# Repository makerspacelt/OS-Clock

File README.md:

# OS-Clock
Repository has information off how to build big portable LED clock.

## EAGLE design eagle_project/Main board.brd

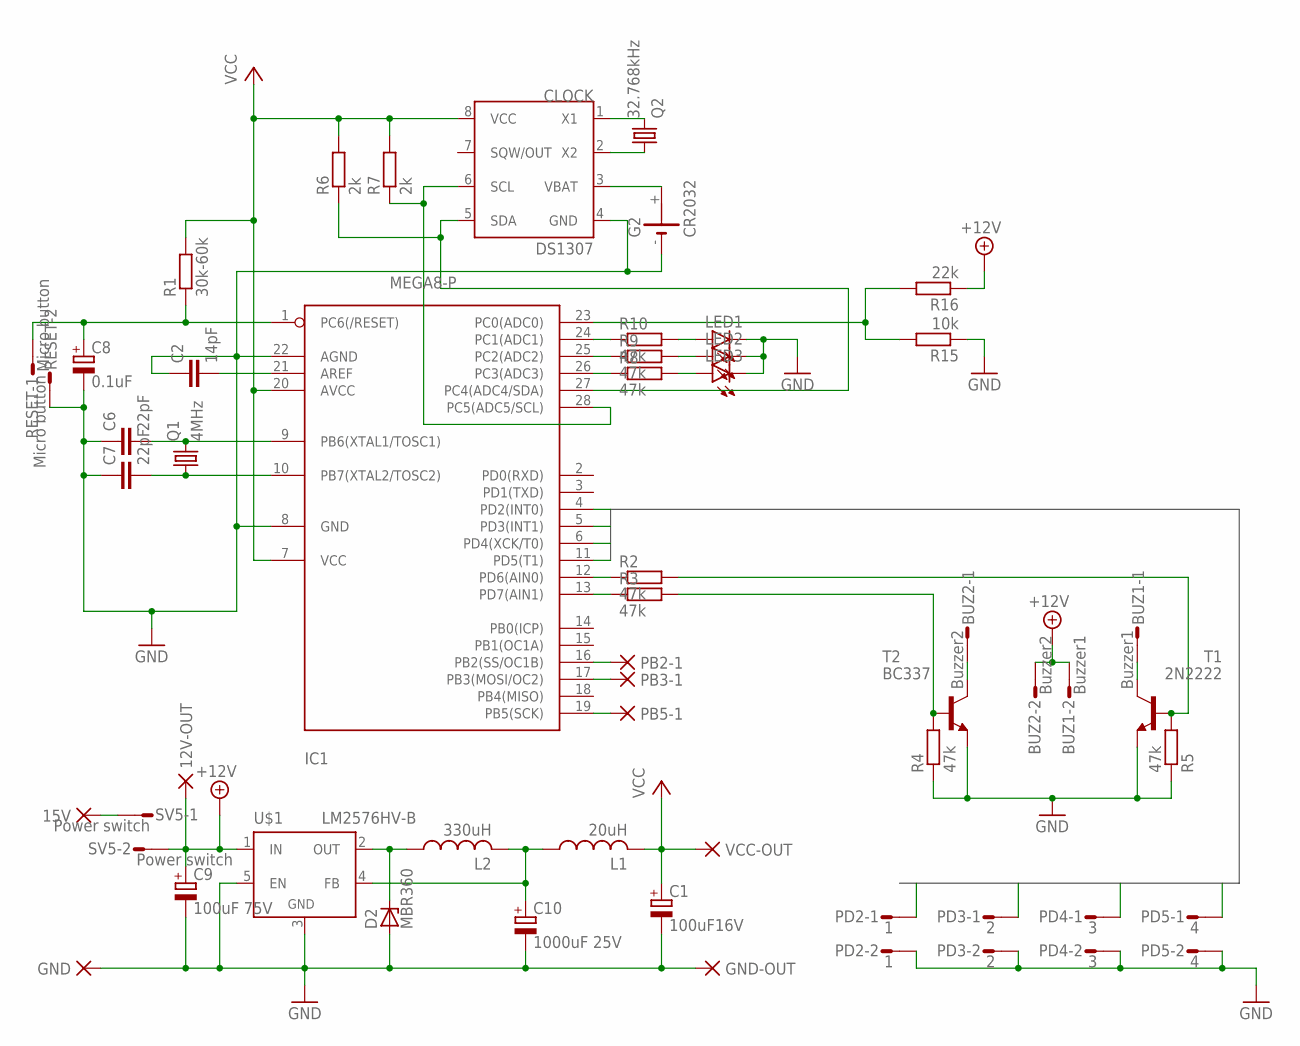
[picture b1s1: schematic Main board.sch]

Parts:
12V-OUT, 15V: PAD-0500; 0500
BUZ1: Buzzer1; S02P
BUZ2: Buzzer2; S02P
C1: 100uF16V; E2,5-6
C2: 14pF; C102-054X133
C6, C7: 22pF; C025-030X050
C8: 0.1uF; E2,5-6
C9: 100uF 75V; E5-10,5
C10: 1000uF 25V; E5-10,5
CLOCK: DS1307; SOIC-8
D2: MBR360; C1702-15
G2: CR2032; CR2032-20MM
GND: PAD-0500; 0500
GND-OUT: PAD-0500; 0500
IC1: MEGA8-P; DIL28-3
L1: 20uH; TJ3-U1
L2: 330uH; TJ3-U1
LED1, LED2, LED3: LED5MM
PB2-1, PB3-1, PB5-1: PAD-0400; 0400
PD2: 1; S02P
PD3: 2; S02P
PD4: 3; S02P
PD5: 4; S02P
Q1: 4MHz; HC49U-V
Q2: 32.768kHz; CRYSTAL
R1: 30k-60k; 0309/15
R2, R3, R4, R5, R8, R9, R10: 47k; 0309/15
R6, R7: 2k; 0309/15
R15: 10k; 0309/15
R16: 22k; 0309/15
RESET: Micro button; S02P
SV5: Power switch; S02P
T1: 2N2222; TO18
T2: BC337; TO92
U$1: LM2576HV-B; TO220-53
VCC-OUT: PAD-0500; 0500

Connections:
+12V: 12V-OUT.P$1, BUZ1.2, BUZ2.2, C9.+, R16.1, SV5.2, U$1.1 (IN)
GND: C1.-, C2.1, C6.1, C7.1, C8.-, C9.-, C10.-, CLOCK.4 (GND), D2.A, G2.-, GND.P$1, GND-OUT.P$1, IC1.8 (GND), IC1.22 (AGND), LED1.K (C), LED2.K (C), LED3.K (C), PD2.2, PD3.2, PD4.2, PD5.2, R4.1, R5.1, R15.1, RESET.2, T1.1 (E), T2.1 (E), U$1.3 (GND), U$1.5 (EN)
unnamed: CLOCK.1 (X1), Q2.2
unnamed: 15V.P$1, SV5.1
unnamed: CLOCK.2 (X2), Q2.1
unnamed: IC1.24 (PC1(ADC1)), R10.1
unnamed: IC1.25 (PC2(ADC2)), R9.1
unnamed: IC1.26 (PC3(ADC3)), R8.1
unnamed: LED1.A, R10.2
unnamed: LED2.A, R9.2
unnamed: LED3.A, R8.2
unnamed: C2.2, IC1.21 (AREF)
unnamed: C6.2, IC1.9 (PB6(XTAL1/TOSC1)), Q1.2
unnamed: C7.2, IC1.10 (PB7(XTAL2/TOSC2)), Q1.1
unnamed: C8.+, IC1.1 (PC6(/RESET)), R1.1, RESET.1
unnamed: CLOCK.6 (SCL), IC1.28 (PC5(ADC5/SCL)), R7.1
unnamed: IC1.23 (PC0(ADC0)), R15.2, R16.2
unnamed: CLOCK.5 (SDA), IC1.27 (PC4(ADC4/SDA)), R6.1
unnamed: IC1.12 (PD6(AIN0)), R2.1
unnamed: IC1.13 (PD7(AIN1)), R3.1
unnamed: BUZ2.1, T2.3 (C)
unnamed: R3.2, R4.2, T2.2 (B)
unnamed: R2.2, R5.2, T1.2 (B)
unnamed: BUZ1.1, T1.3 (C)
unnamed: IC1.16 (PB2(SS/OC1B)), PB2-1.P$1
unnamed: C10.+, L1.1, L2.2, U$1.4 (FB)
unnamed: D2.C, L2.1, U$1.2 (OUT)
unnamed: IC1.17 (PB3(MOSI/OC2)), PB3-1.P$1
unnamed: IC1.19 (PB5(SCK)), PB5-1.P$1
PD2: IC1.4 (PD2(INT0)), PD2.1
PD3: IC1.5 (PD3(INT1)), PD3.1
PD4: IC1.6 (PD4(XCK/T0)), PD4.1
PD5: IC1.11 (PD5(T1)), PD5.1
VBAT: CLOCK.3 (VBAT), G2.+
VCC: C1.+, CLOCK.8 (VCC), IC1.7 (VCC), IC1.20 (AVCC), L1.2, R1.2, R6.2, R7.2, VCC-OUT.P$1

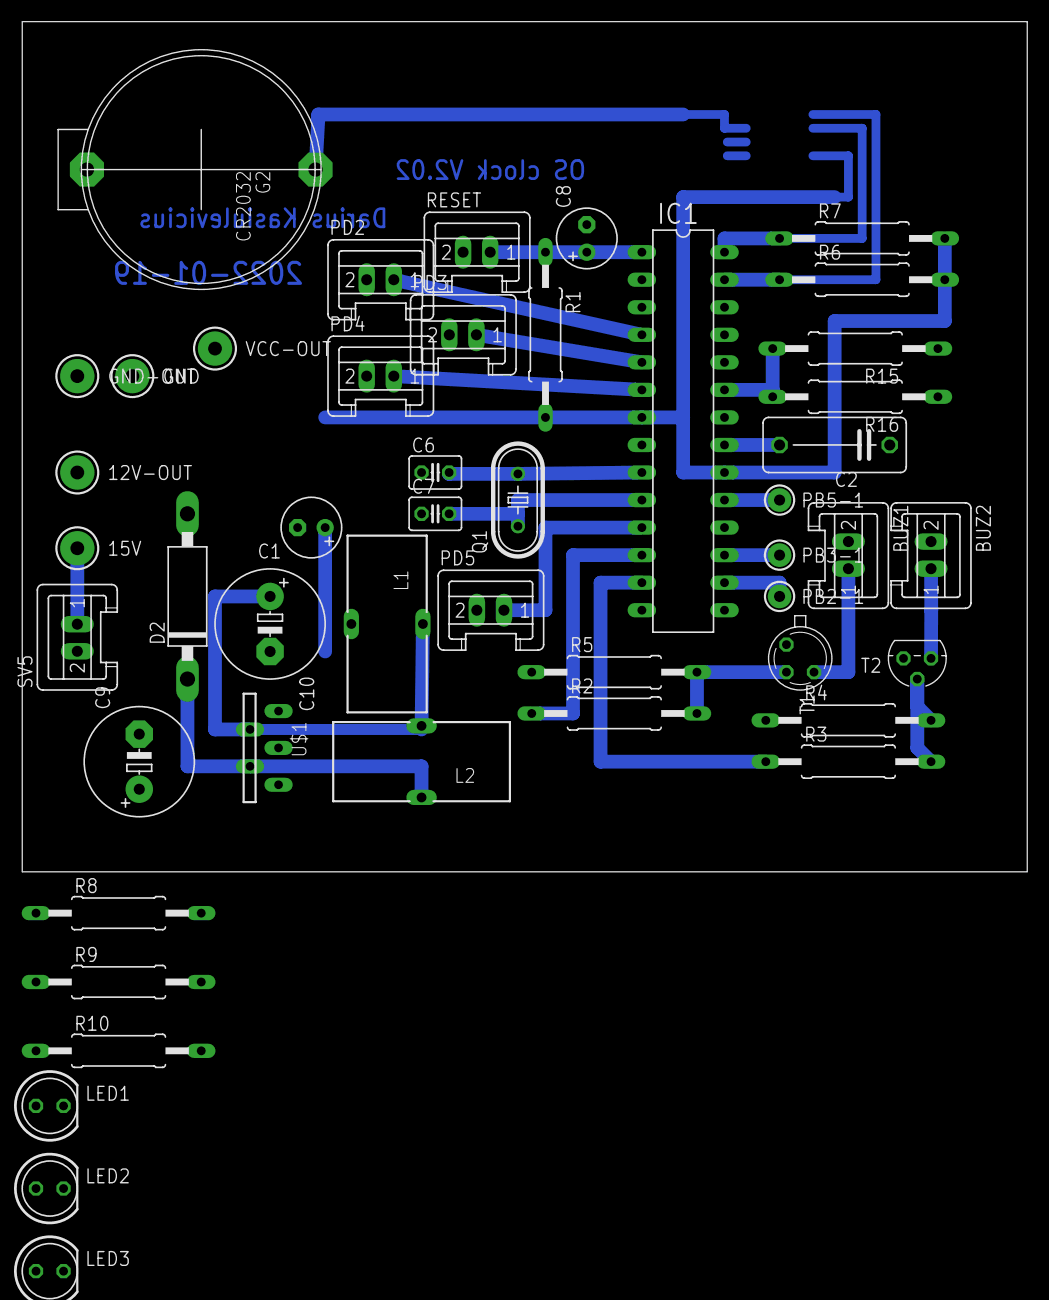
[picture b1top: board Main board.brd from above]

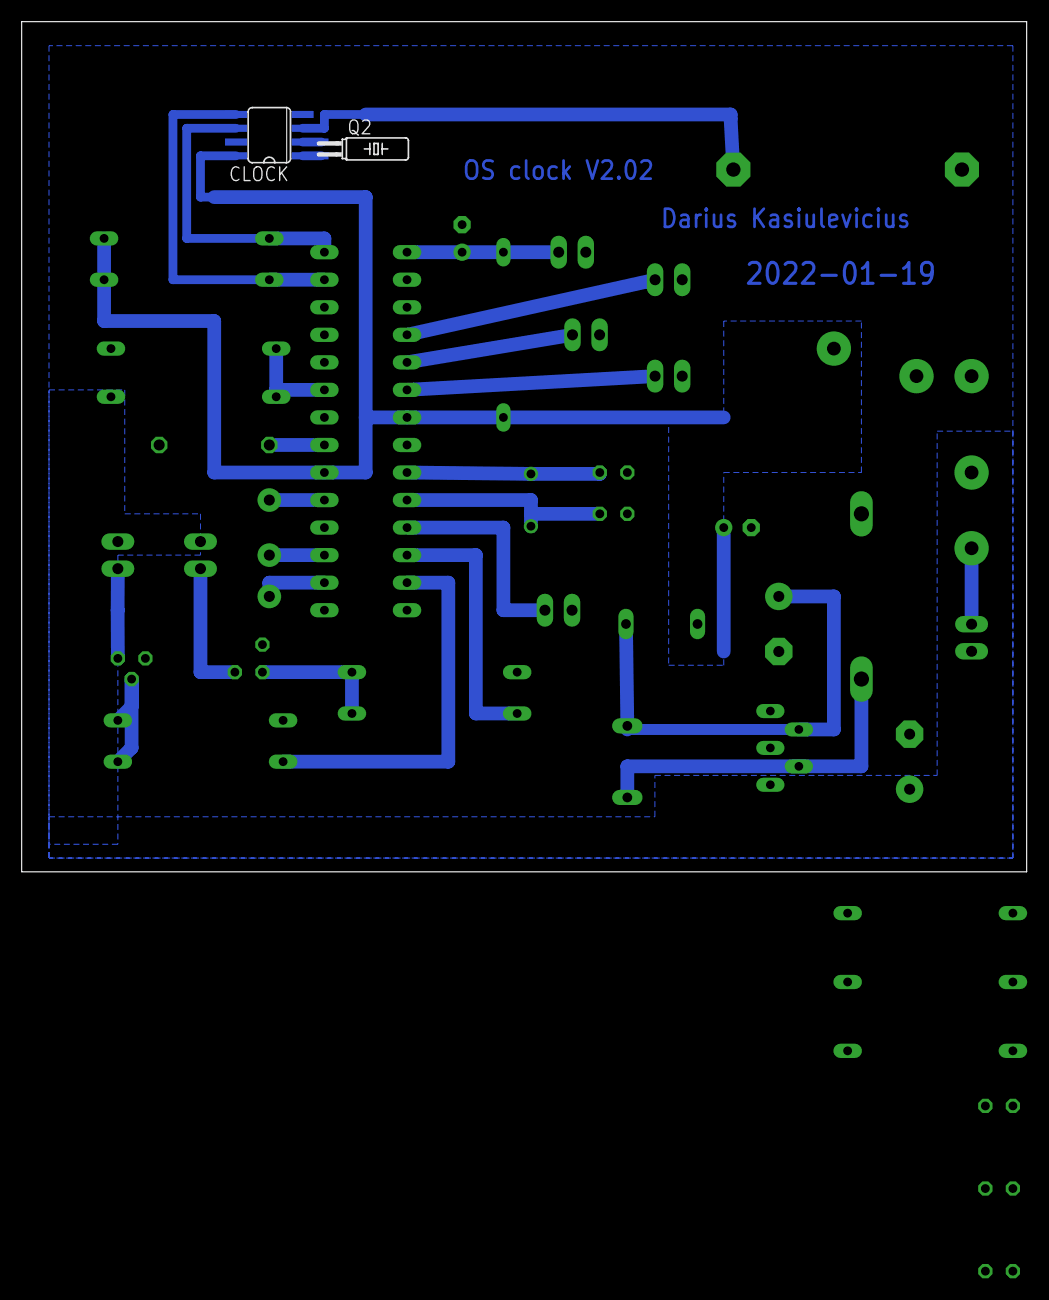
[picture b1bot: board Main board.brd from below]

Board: 2 copper layers, 92.7 x 78.4 mm, 49 parts (2 on the bottom side), 35 nets.

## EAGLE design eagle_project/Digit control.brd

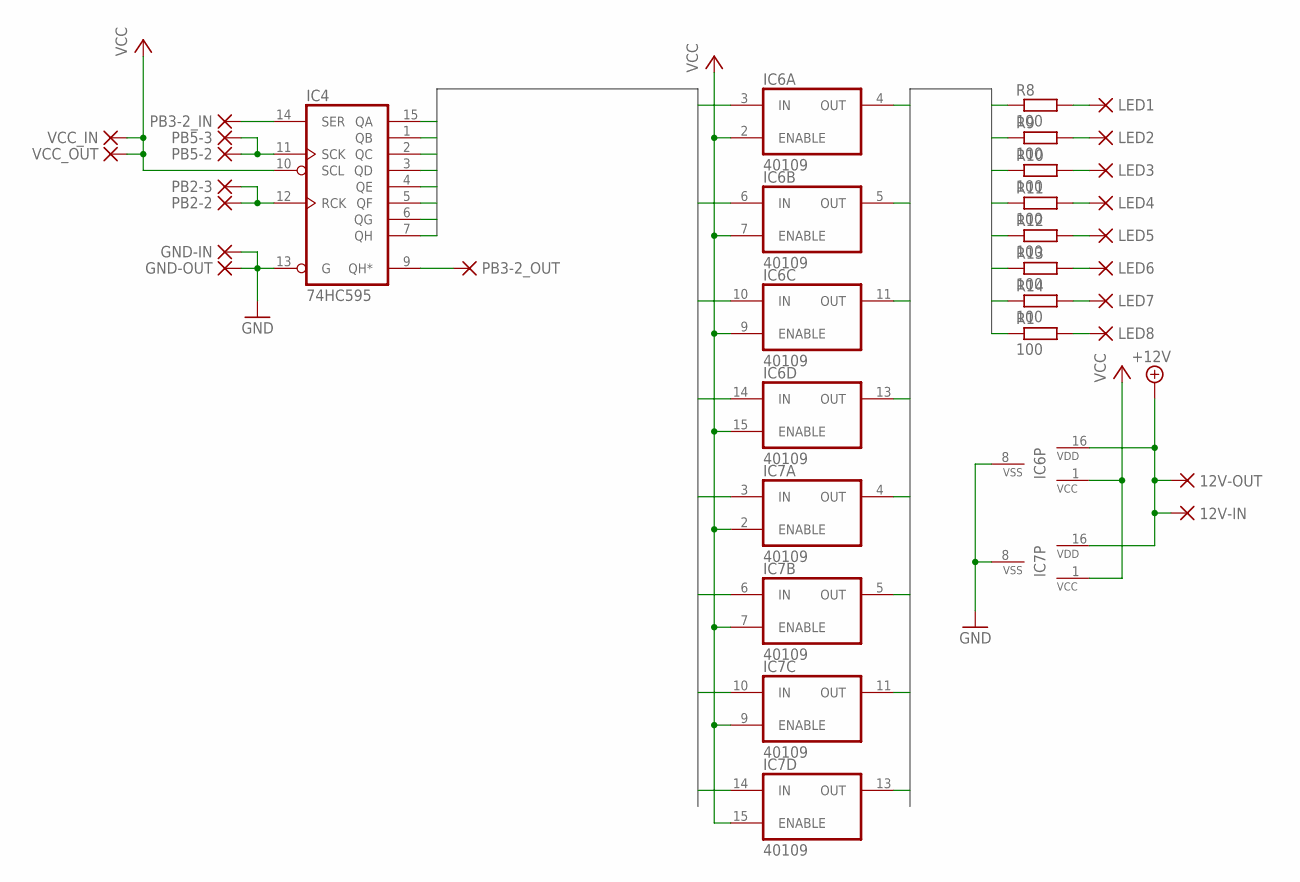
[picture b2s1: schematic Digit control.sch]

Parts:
12V-IN, 12V-OUT: PAD-0500; 0500
GND-IN: PAD-0500; 0500
GND-OUT: PAD-0820; 0820
IC4: 74HC595; DIL16
IC6, IC7: 40109; DIL16
LED1, LED2, LED3, LED4, LED5, LED6, LED7, LED8: PAD-0400; 0400
PB2-2, PB2-3, PB3-2_IN, PB3-2_OUT, PB5-2, PB5-3: PAD-0400; 0400
R1, R8, R9, R10, R11, R12, R13, R14: 100; 0309/15
VCC_IN: PAD-0500; 0500
VCC_OUT: PAD-0500; 0500

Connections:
+12V: 12V-IN.P$1, 12V-OUT.P$1, IC6.16 (VDD), IC7.16 (VDD)
GND: GND-IN.P$1, GND-OUT.P$1, IC4.8 (GND), IC4.13 (G), IC6.8 (VSS), IC7.8 (VSS)
LED1: IC6.4 (OUT), R8.1
LED2: IC6.5 (OUT), R9.1
LED3: IC6.11 (OUT), R10.1
LED4: IC6.13 (OUT), R11.1
LED5: IC7.4 (OUT), R12.1
LED6: IC7.5 (OUT), R13.1
LED7: IC7.11 (OUT), R14.1
LED8: IC7.13 (OUT), R1.1
LED_INPUT1: IC4.15 (QA), IC6.3 (IN)
LED_INPUT2: IC4.1 (QB), IC6.6 (IN)
LED_INPUT3: IC4.2 (QC), IC6.10 (IN)
LED_INPUT4: IC4.3 (QD), IC6.14 (IN)
LED_INPUT5: IC4.4 (QE), IC7.3 (IN)
LED_INPUT6: IC4.5 (QF), IC7.6 (IN)
LED_INPUT7: IC4.6 (QG), IC7.10 (IN)
LED_INPUT8: IC4.7 (QH), IC7.14 (IN)
unnamed: IC4.14 (SER), PB3-2_IN.P$1
unnamed: LED1.P$1, R8.2
unnamed: IC4.11 (SCK), PB5-2.P$1, PB5-3.P$1
unnamed: IC4.12 (RCK), PB2-2.P$1, PB2-3.P$1
unnamed: IC4.9 (QH*), PB3-2_OUT.P$1
unnamed: LED7.P$1, R14.2
unnamed: LED6.P$1, R13.2
unnamed: LED5.P$1, R12.2
unnamed: LED4.P$1, R11.2
unnamed: LED3.P$1, R10.2
unnamed: LED2.P$1, R9.2
unnamed: LED8.P$1, R1.2
VCC: IC4.10 (SCL), IC4.16 (VCC), IC6.1 (VCC), IC6.2 (ENABLE), IC6.7 (ENABLE), IC6.9 (ENABLE), IC6.15 (ENABLE), IC7.1 (VCC), IC7.2 (ENABLE), IC7.7 (ENABLE), IC7.9 (ENABLE), IC7.15 (ENABLE), VCC_IN.P$1, VCC_OUT.P$1

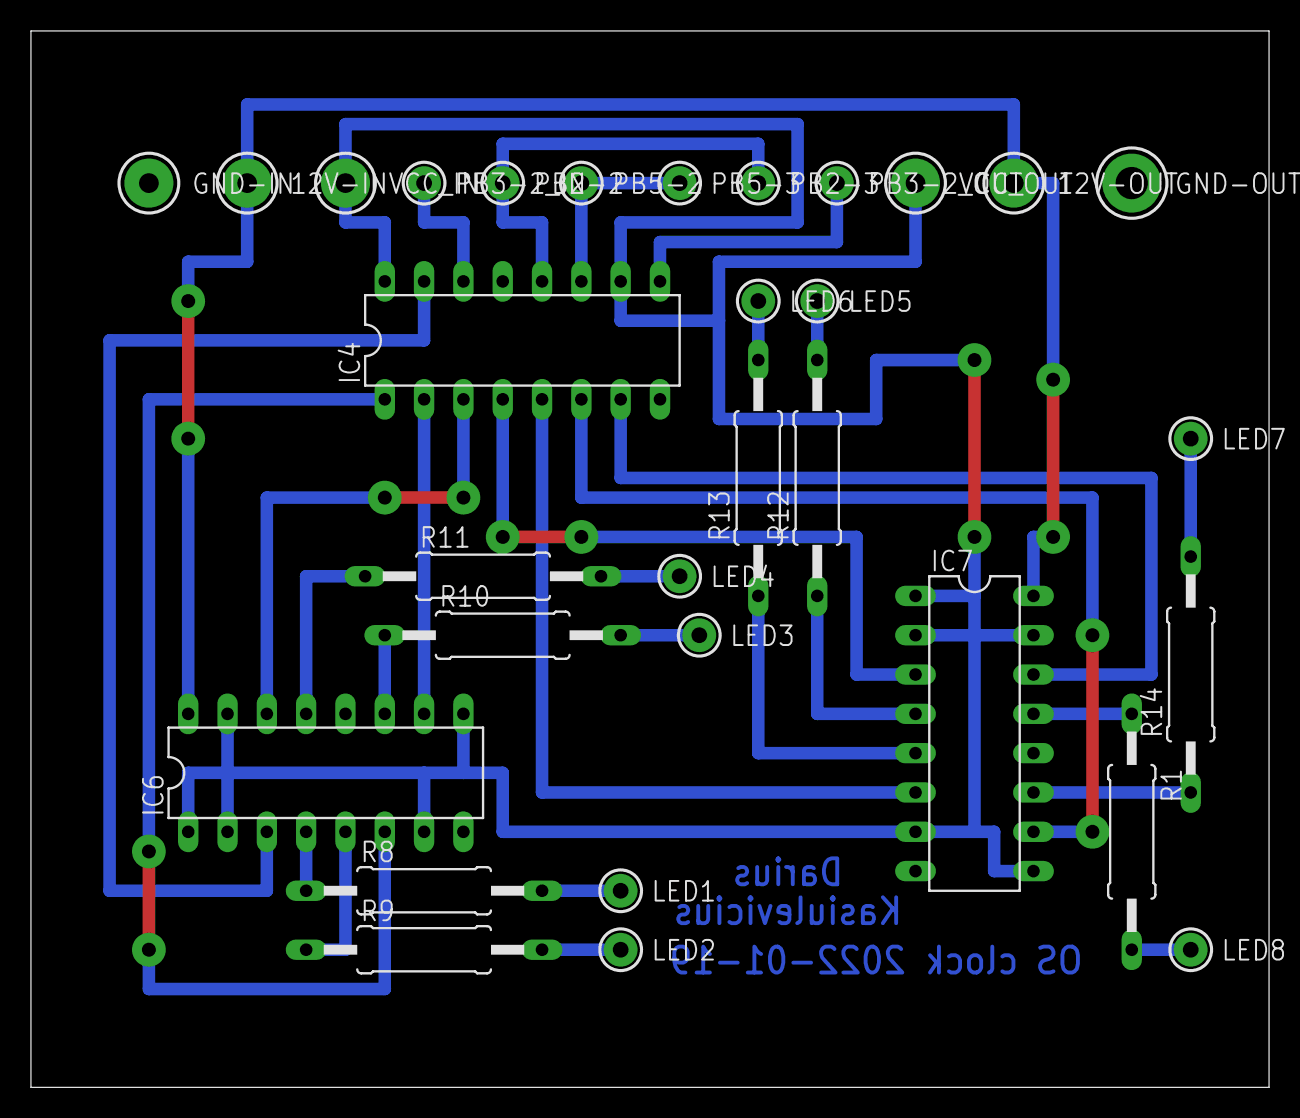
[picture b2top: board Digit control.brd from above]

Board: 2 copper layers, 80.0 x 68.2 mm, 31 parts (0 on the bottom side), 31 nets.

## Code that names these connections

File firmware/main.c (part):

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#define FALSE 0
#define TRUE 1

#define PRESSED_UP      0x10    // sv3 up       - atmega pin 6   PD4
#define PRESSED_DOWN    0x04    // sv1 down     - atmega pin 4   PD2 INT0
#define PRESSED_ENTER   0x08    // sv2 left     - atmega pin 5   PD3 INT1
#define PRESSED_CANCEL  0x20    // sv4 right    - atmega pin 11  PD5

#define LED_GREEN   PC3    // atmega pin 26
#define LED_YELLOW  PC2    // atmega pin 25
#define LED_RED     PC1    // atmega pin 24

#define BATTERY_YELLOW_LEVEL  70 // 60 70
#define BATTERY_RED_LEVEL     58 // 40 58

#define BUZZER_LONG     PD6     // PD6
#define BUZZER_SHORT    PD7     // PD7

#define STATUS_REAL_TIME        0x00
#define STATUS_CONFIG_MENU      0x01
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    PORTD = 0x00;

    //SLA and SLC pins sets
    DDRC &= ~((1 << PC4) | (1 << PC5));  // Make sure pins are inputs (or untouched)
    PORTC &= ~((1 << PC4) | (1 << PC5));  // Don’t enable internal pullups unless testing

    // set buttons as input
    DDRD &= ~((1<<PD2)|(1<<PD3)|(1<<PD4)|(1<<PD5));
    PORTD |= (1<<PD2)|(1<<PD3)|(1<<PD4)|(1<<PD5);
    // enable pull up resistors
    MCUCR &= ~(1<<PUD);
}
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void initFeatures(void)
{
    //Configure ADC
    DDRC &= ~(1<<PC0);
    ADMUX = (0<<REFS1)|(1<<REFS0)|(0<<ADLAR)|(0<<MUX3)|(0<<MUX2)|(0<<MUX1)|(0<<MUX0); //ADC0 is connected to battery
    ADCSRA = (1<<ADEN)|(0<<ADATE)|(0<<ADIF)|(0<<ADIE)|(1<<ADPS2)|(1<<ADPS1)|(0<<ADPS0); //Accuracy is best between 50 and 200 Khz clock frequency.

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void renewDisplay(void)
{
    // display data
    PORTB |= (1<<PB2);
    PORTB &= ~(1<<PB2);
}

void clearDisplay(void)
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
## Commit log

2015-03-02 OS-clock v1 backup
2015-03-02 Added v1 screen shot off schematics and boards
2015-03-02 Added eagle custom library which are used on project
2015-03-02 Moved images to seperate folder
2015-03-02 Backup v1 firmware
2015-03-02 Backup v1 documentation
2015-03-02 V2.x initial commit
2015-03-02 v2.x eagle project
2015-03-02 Added schematic and board images
2015-03-02 Added printable boards
2015-08-20 Created test code
2015-08-24 Added git ignore file
2015-08-24 Adopted makefile to OSX environment with Arduino IDE
2015-08-24 Display time from RTC
2015-08-24 Fixed read minutes from RTC
2015-08-25 Defined buttons
2015-08-26 Implemented interupts and buttons push
2015-08-27 Deleted test code line
2015-09-06 Added full menu control
2015-09-07 Added ignore folder
2015-09-07 Replaced tabs with spaces
2015-09-07 Created device setting structure
2015-09-07 Created beep method
2015-09-07 Renamed cariable for better readability
2015-09-09 Code cleanup
2015-09-09 Implemented start from zero time
2015-09-12 Added setting save and read possibility
2015-09-13 Fixed time calculation, when start time is greater then real time
2015-09-13 Implemented start from plus time
2015-09-13 Added display minus sign
2015-09-14 Fixed display without hours zero
2015-09-16 Implemented reset factory
2015-09-16 Implemented start from minus time
2015-09-17 Fixed minus time start
2015-09-17 Added reset time to factory clear
2015-09-18 Added reset time to factory reset
2016-06-18 Changed variables name
2018-08-15 Created read device instructions
2018-08-15 Save real time start on device
2018-08-15 Fixed start from plus time
2018-08-15 Fixed start from minus time
2018-08-15 Removed temporary RTC reset
2018-08-15 Fixed minus time calculation
2018-08-15 Changed calculation as microcontroler can't handle without tmp variable
2018-08-15 Added function to help debugging
2018-08-15 Fixed start minus time calculation logic
2018-08-15 Implemented long beeps count change
2018-08-15 Changes constant name
2018-08-15 Tuning code
2018-08-15 Implemented short beeps count change
2018-08-15 Added comment
2018-08-15 Code is reformatted
2018-08-15 Save real time show
2018-08-15 Fixed mess with status changing
2018-08-15 Fixed buzzer actions
2018-08-15 Changed numbers to constants
2018-11-17 Created alphabet
2018-11-17 Added hello text on start
2019-02-12 Created demo menu
2019-02-26 Removed redundant code
2019-02-26 Fixed small issues
2019-02-26 Created beeps configuration
2019-03-07 Fixed bugs
2019-03-07 Changed hello text
2019-03-13 Deleted redundant code
2019-03-13 Implemented delta time editing
2019-03-13 Moved specific code to separate method
2019-03-13 Implemented real time configuration
2019-03-15 Implemented battery level measurement
2019-03-17 Created user manual in lithuanian
2019-09-08 Added temporary debug mode
2019-09-08 Improved debug mode
2019-09-08 Changed that use 24h clock
2019-09-15 Adjusted debug mode
2019-09-15 Aligned battery level for specific battery
2019-09-15 Enabled nice hello message
2023-01-29 Init commit for atmega 168
2023-01-29 Added latest schema
2023-02-12 feat: Low battery initial commit
2023-02-12 feat: Block clock if battery level is low
2023-02-13 feat: Adjusted constants for low battery
2023-02-19 feat: Added cycle count hidden
2023-02-19 Moved setting to correct count
2025-02-10 Copy from Trimako clock
2025-04-03 Adjustments by clock
2025-05-13 Make upload if data with biggest speed
2025-05-13 Adjusted code on last repair
2025-05-15 Adjusted code on last issues
